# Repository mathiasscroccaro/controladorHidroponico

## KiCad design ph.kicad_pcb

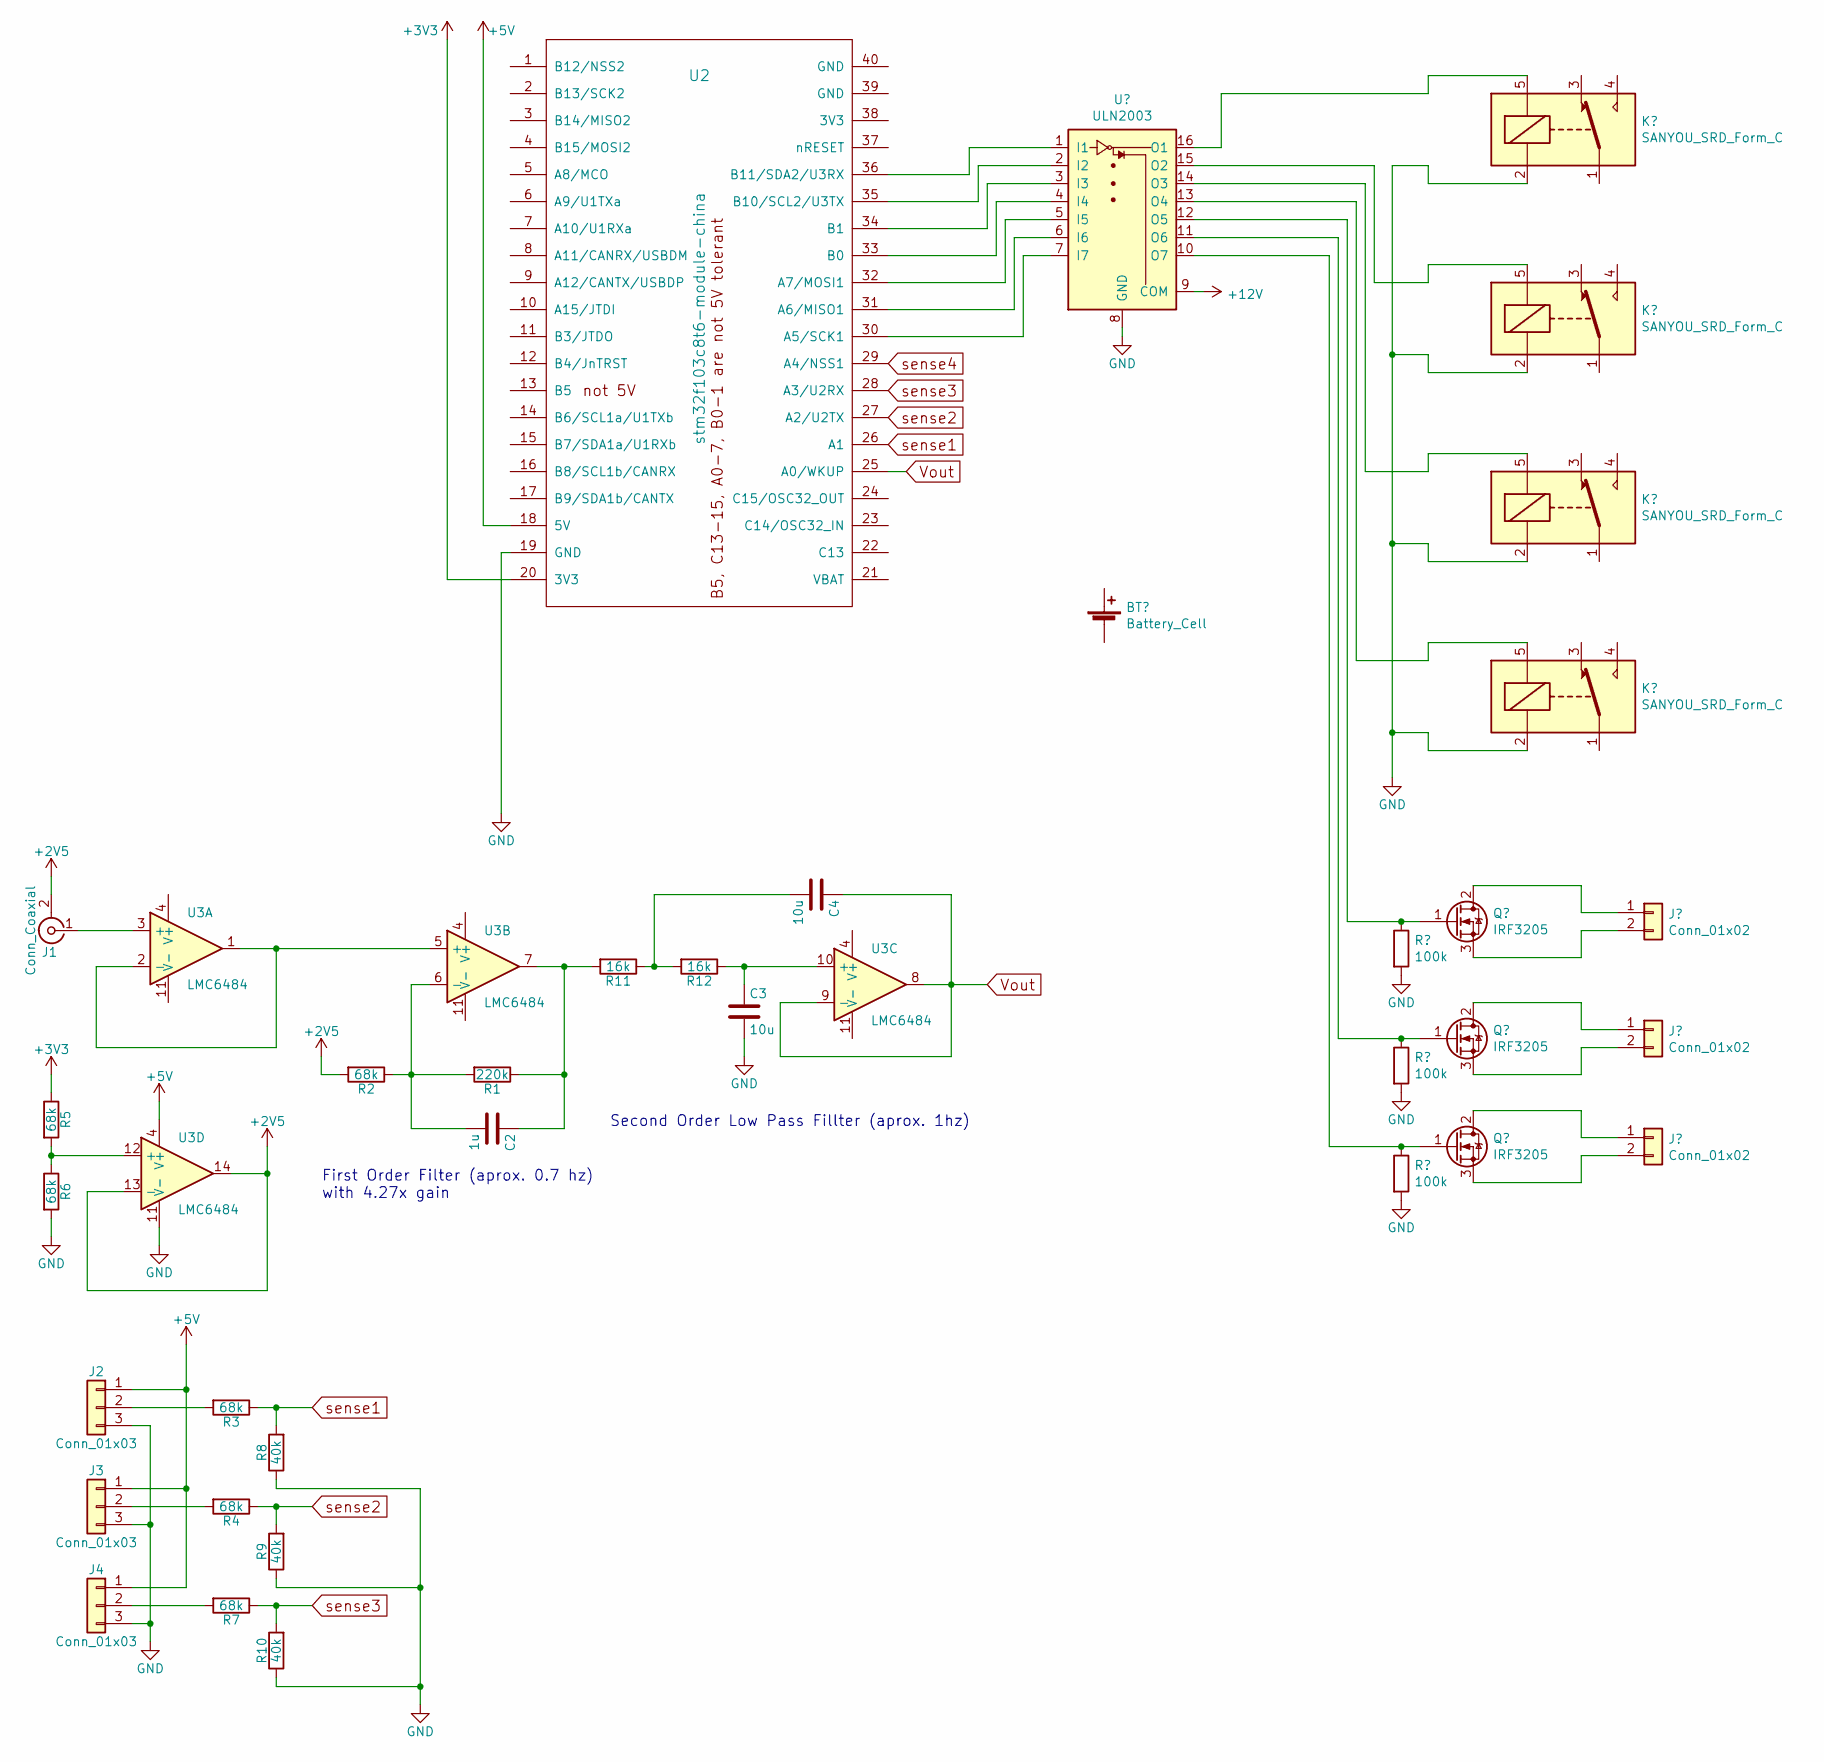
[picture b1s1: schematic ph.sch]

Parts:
C2: 1u; C_1206_HandSoldering
C3, C4: 10u; C_1206_HandSoldering
J1: Conn_Coaxial; Pin_Header_Angled_1x02_Pitch2.54mm
J2, J3, J4: Conn_01x03; JST_NV_B03P-NV_3x5.00mm_Vertical
R1: 220k; R_1206_HandSoldering
R2, R3, R4, R5, R6, R7: 68k; R_1206_HandSoldering
R8, R9, R10: 40k; R_1206_HandSoldering
R11, R12: 16k; R_1206_HandSoldering
U2: stm32f103c8t6-module-china; DIP-40_W15.24mm_LongPads
U3: LMC6484; SOIC-14_3.9x8.7mm_Pitch1.27mm

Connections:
+2V5: J1.2 (Ext), R2.2, U3.13 (-), U3.14
+3V3: R5.1, U2.20 (3V3); also elsewhere on the board
+5V: J2.1, J3.1, J4.1, U2.18 (5V), U3.4 (V+); also elsewhere on the board
GND: C3.2, J2.3, J3.3, J4.3, R6.2, R8.1, R9.1, R10.1, U2.19 (GND), U3.11 (V-); also elsewhere on the board
unnamed: C2.1, R1.1, R11.2, U3.7
unnamed: C2.2, R1.2, R2.1, U3.6 (-)
unnamed: C3.1, R12.1, U3.10 (+)
unnamed: C4.2, R11.1, R12.2
unnamed: J1.1 (In), U3.3 (+)
unnamed: J2.2, R3.2
unnamed: J3.2, R4.2
unnamed: J4.2, R7.2
unnamed: R5.2, R6.1, U3.12 (+)
unnamed 13: U2.1 (B12/NSS2); also elsewhere on the board
unnamed 14: U2.2 (B13/SCK2); also elsewhere on the board
unnamed 15: U2.3 (B14/MISO2); also elsewhere on the board
unnamed 16: U2.4 (B15/MOSI2); also elsewhere on the board
unnamed 17: U2.5 (A8/MCO); also elsewhere on the board
unnamed 18: U2.6 (A9/U1TXa); also elsewhere on the board
unnamed 19: U2.7 (A10/U1RXa); also elsewhere on the board
unnamed 20: U2.8 (A11/CANRX/USBDM); also elsewhere on the board
unnamed 21: U2.9 (A12/CANTX/USBDP); also elsewhere on the board
unnamed 22: U2.10 (A15/JTDI); also elsewhere on the board
unnamed 23: U2.11 (B3/JTDO); also elsewhere on the board
unnamed 24: U2.12 (B4/JnTRST); also elsewhere on the board
unnamed 25: U2.13 (B5); also elsewhere on the board
unnamed 26: U2.14 (B6/SCL1a/U1TXb); also elsewhere on the board
unnamed 27: U2.15 (B7/SDA1a/U1RXb); also elsewhere on the board
unnamed 28: U2.16 (B8/SCL1b/CANRX); also elsewhere on the board
unnamed 29: U2.17 (B9/SDA1b/CANTX); also elsewhere on the board
unnamed 30: U2.21 (VBAT); also elsewhere on the board
unnamed 31: U2.22 (C13); also elsewhere on the board
unnamed 32: U2.23 (C14/OSC32_IN); also elsewhere on the board
unnamed 33: U2.24 (C15/OSC32_OUT); also elsewhere on the board
unnamed 39: U2.30 (A5/SCK1); also elsewhere on the board
unnamed 40: U2.31 (A6/MISO1); also elsewhere on the board
unnamed 41: U2.32 (A7/MOSI1); also elsewhere on the board
unnamed 42: U2.33 (B0); also elsewhere on the board
unnamed 43: U2.34 (B1); also elsewhere on the board
unnamed 44: U2.35 (B10/SCL2/U3TX); also elsewhere on the board
unnamed 45: U2.36 (B11/SDA2/U3RX); also elsewhere on the board
unnamed 46: U2.37 (nRESET); also elsewhere on the board
unnamed 47: U2.38 (3V3); also elsewhere on the board
unnamed 48: U2.39 (GND); also elsewhere on the board
unnamed 49: U2.40 (GND); also elsewhere on the board
unnamed: U3.1, U3.2 (-), U3.5 (+)
Vout: C4.1, U2.25 (A0/WKUP), U3.8, U3.9 (-)
sense1: R3.1, R8.2, U2.26 (A1)
sense2: R4.1, R9.2, U2.27 (A2/U2TX)
sense3: R7.1, R10.2, U2.28 (A3/U2RX)
sense4: U2.29 (A4/NSS1)

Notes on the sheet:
Second Order Low Pass Fillter (aprox. 1hz)
First Order Filter (aprox. 0.7 hz) with 4.27x gain

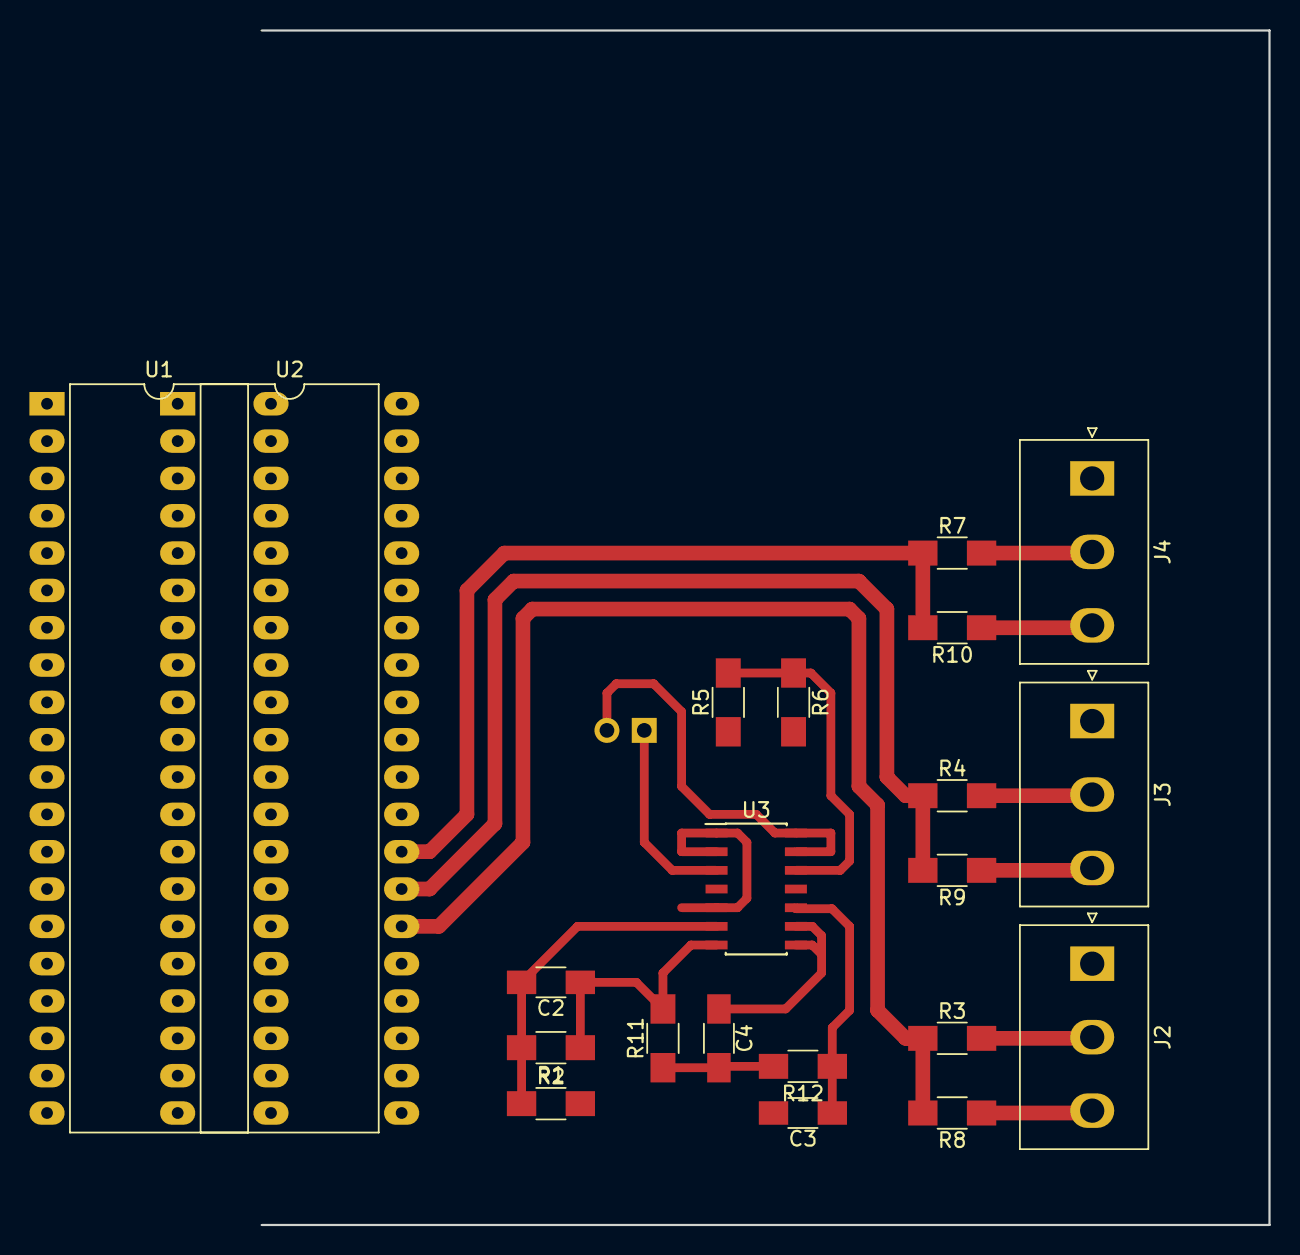
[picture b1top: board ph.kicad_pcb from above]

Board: 2 copper layers, 68.6 x 81.3 mm, 22 parts (1 on the bottom side), 50 nets.

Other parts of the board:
U1: stm32f103c8t6-module-china; DIP-40_W15.24mm_LongPads

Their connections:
+3V3: U1.20; also elsewhere on the board
+5V: U1.18; also elsewhere on the board
GND: U1.19; also elsewhere on the board
unnamed 13: U1.1; also elsewhere on the board
unnamed 14: U1.2; also elsewhere on the board
unnamed 15: U1.3; also elsewhere on the board
unnamed 16: U1.4; also elsewhere on the board
unnamed 17: U1.5; also elsewhere on the board
unnamed 18: U1.6; also elsewhere on the board
unnamed 19: U1.7; also elsewhere on the board
unnamed 20: U1.8; also elsewhere on the board
unnamed 21: U1.9; also elsewhere on the board
unnamed 22: U1.10; also elsewhere on the board
unnamed 23: U1.11; also elsewhere on the board
unnamed 24: U1.12; also elsewhere on the board
unnamed 25: U1.13; also elsewhere on the board
unnamed 26: U1.14; also elsewhere on the board
unnamed 27: U1.15; also elsewhere on the board
unnamed 28: U1.16; also elsewhere on the board
unnamed 29: U1.17; also elsewhere on the board
unnamed 30: U1.21; also elsewhere on the board
unnamed 31: U1.22; also elsewhere on the board
unnamed 32: U1.23; also elsewhere on the board
unnamed 33: U1.24; also elsewhere on the board
unnamed 39: U1.30; also elsewhere on the board
unnamed 40: U1.31; also elsewhere on the board
unnamed 41: U1.32; also elsewhere on the board
unnamed 42: U1.33; also elsewhere on the board
unnamed 43: U1.34; also elsewhere on the board
unnamed 44: U1.35; also elsewhere on the board
unnamed 45: U1.36; also elsewhere on the board
unnamed 46: U1.37; also elsewhere on the board
unnamed 47: U1.38; also elsewhere on the board
unnamed 48: U1.39; also elsewhere on the board
unnamed 49: U1.40; also elsewhere on the board
